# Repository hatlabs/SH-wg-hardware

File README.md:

# Sailor Hat WiFi Gateway

This repository contains the Sailor Hat WiFi Gateway (SH-wg) hardware design. SH-wg is a purpose-built NMEA 2000 WiFi gateway device.

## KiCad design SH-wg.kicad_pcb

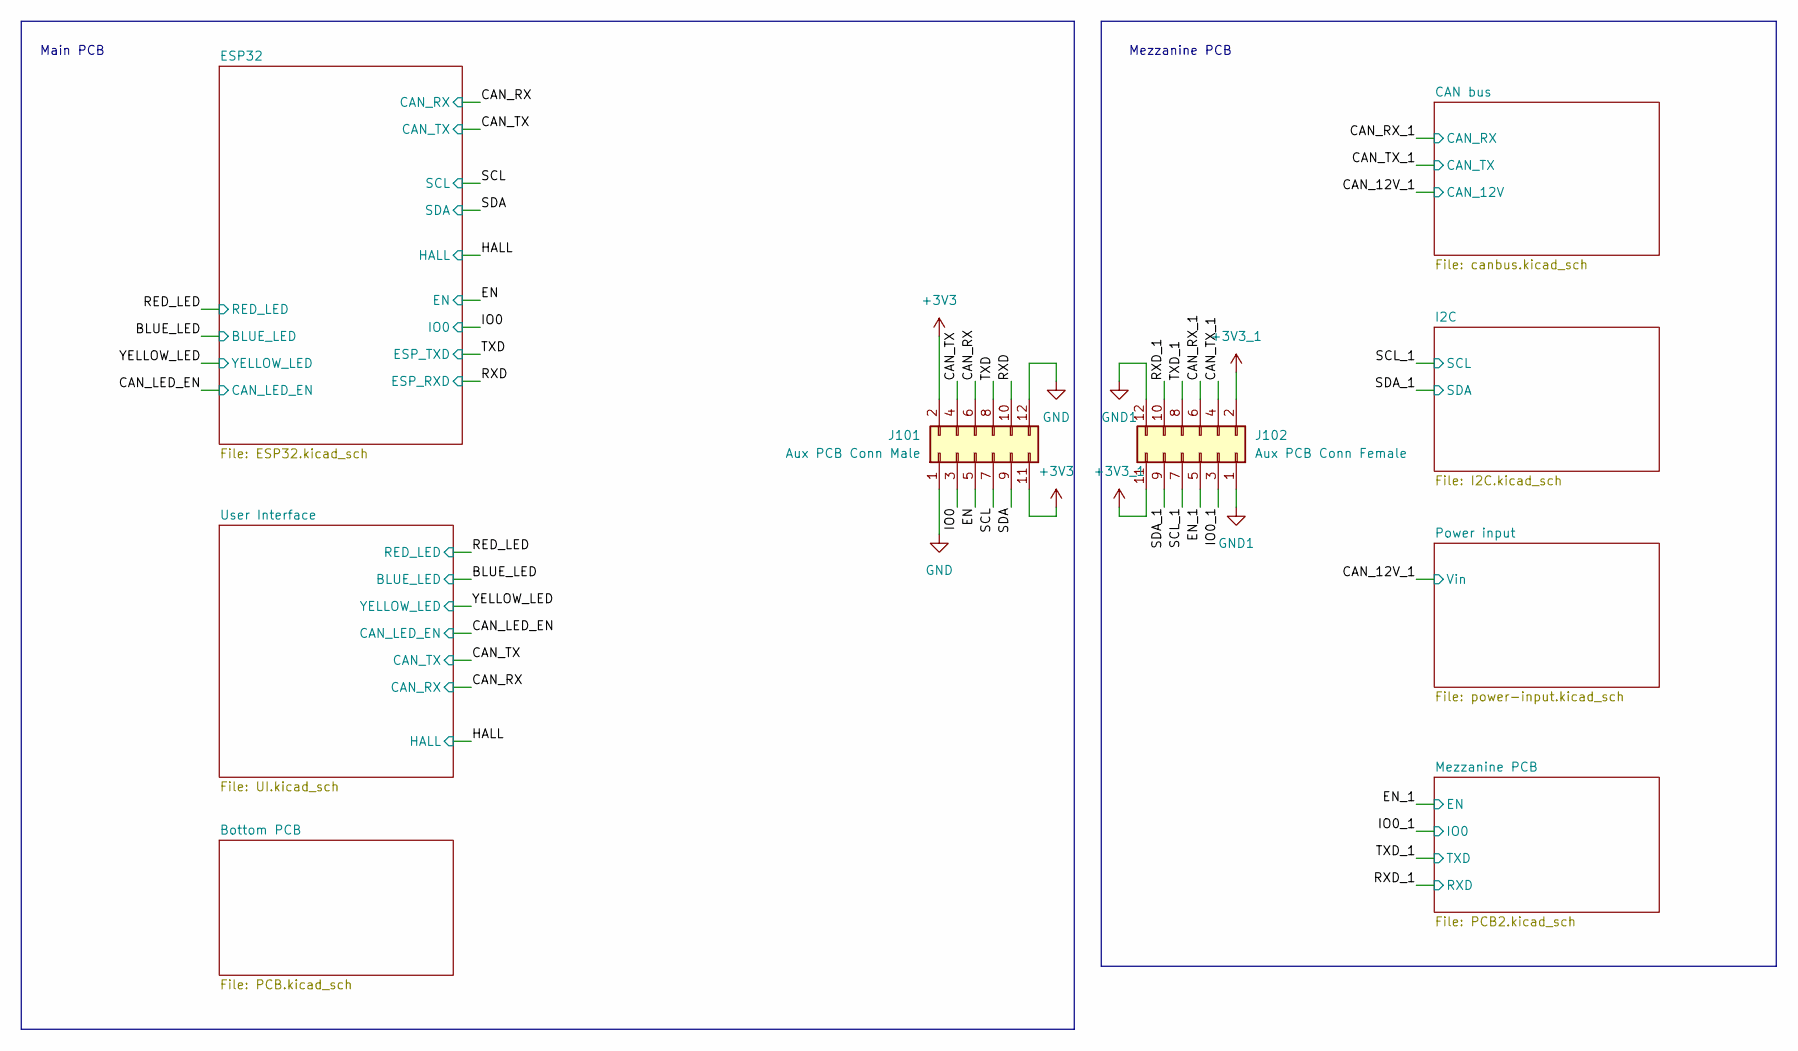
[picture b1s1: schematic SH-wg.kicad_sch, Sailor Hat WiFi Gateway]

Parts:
J101: Aux PCB Conn Male; PinHeader_2x06_P2.54mm_Vertical; LCSC C124388
J102: Aux PCB Conn Female; PinSocket_2x06_P2.54mm_Vertical; LCSC C36191

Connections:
+3V3_1: J102.2, J102.11; also elsewhere on the board
/CAN_RX: J101.6; also elsewhere on the board
/CAN_RX_1: J102.6; also elsewhere on the board
/CAN_TX: J101.4; also elsewhere on the board
/CAN_TX_1: J102.4; also elsewhere on the board
/EN: J101.5; also elsewhere on the board
/EN_1: J102.5; also elsewhere on the board
/IO0: J101.3; also elsewhere on the board
/IO0_1: J102.3; also elsewhere on the board
/RXD: J101.10; also elsewhere on the board
/RXD_1: J102.10; also elsewhere on the board
/SCL: J101.7; also elsewhere on the board
/SCL_1: J102.7; also elsewhere on the board
/SDA: J101.9; also elsewhere on the board
/SDA_1: J102.9; also elsewhere on the board
/TXD: J101.8; also elsewhere on the board
/TXD_1: J102.8; also elsewhere on the board
GND: J101.1, J101.12; also elsewhere on the board
GND1: J102.1, J102.12; also elsewhere on the board

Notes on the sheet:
Mezzanine PCB
Main PCB

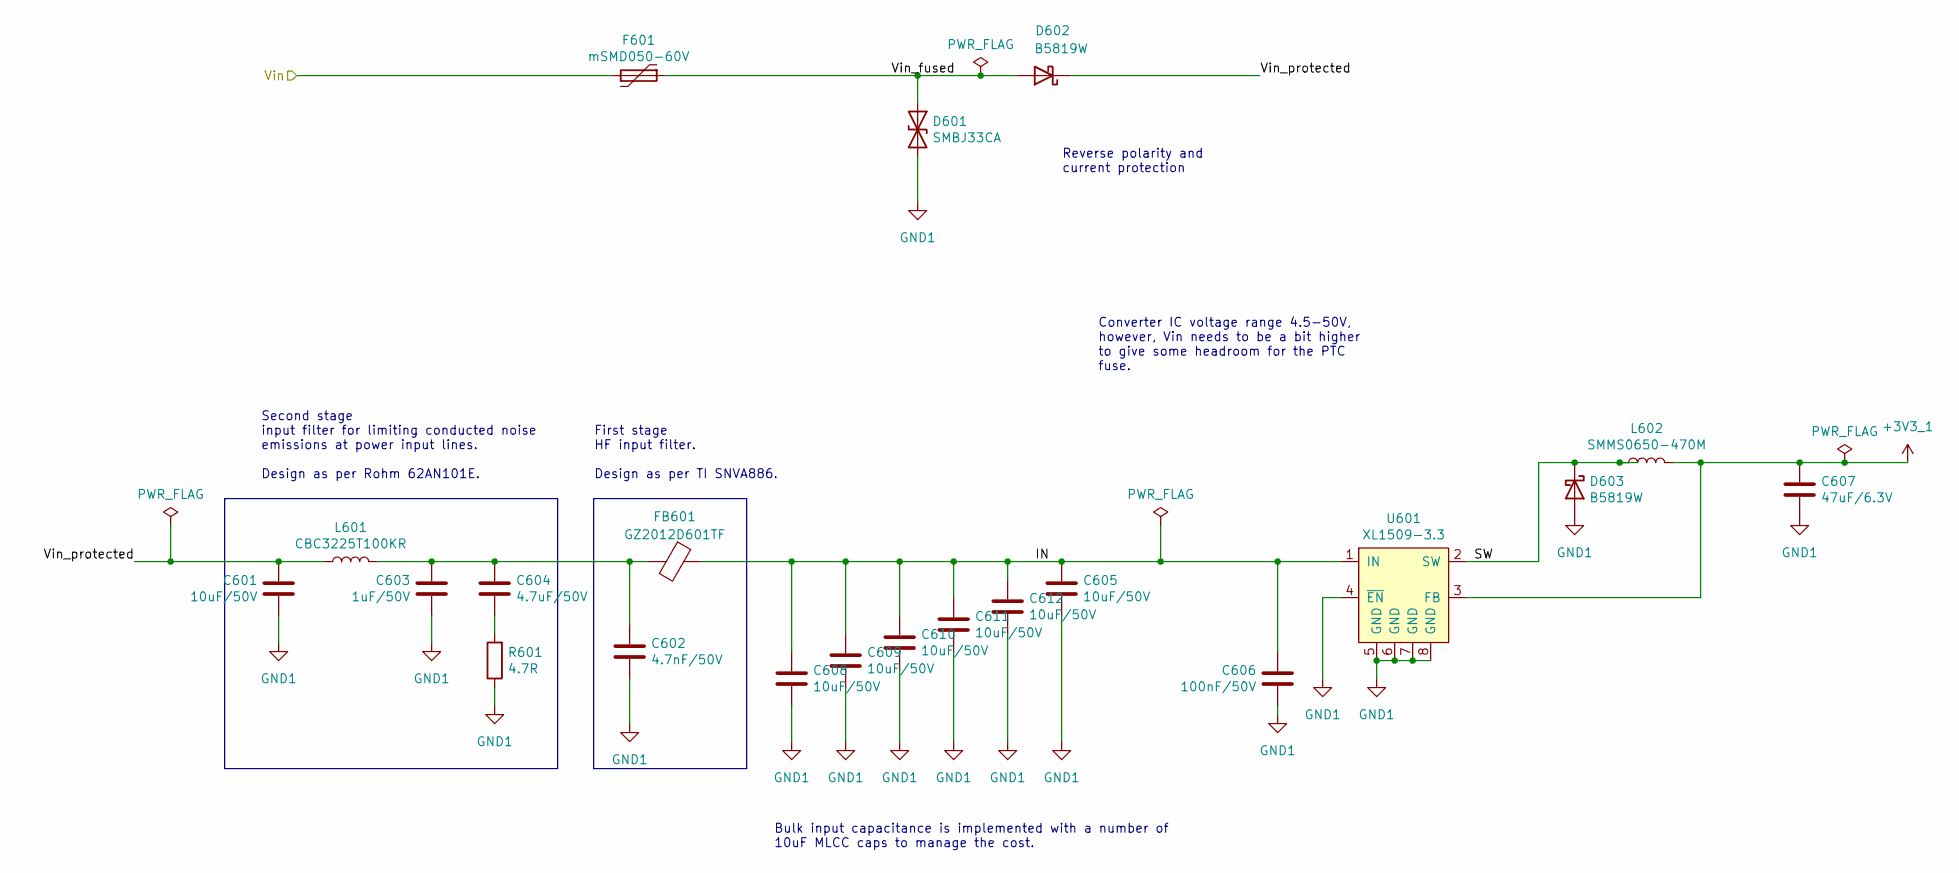
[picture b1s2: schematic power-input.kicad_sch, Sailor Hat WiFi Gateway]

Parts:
C601, C605, C608, C609, C610, C611, C612: 10uF/50V; C_1206_3216Metric; LCSC C13585
C602: 4.7nF/50V; C_0402_1005Metric; LCSC C1538
C603: 1uF/50V; C_0805_2012Metric; LCSC C215803
C604: 4.7uF/50V; C_1206_3216Metric; LCSC C29823
C606: 100nF/50V; C_0402_1005Metric; LCSC C307331
C607: 47uF/6.3V; C_1206_3216Metric; LCSC C96123
D601: SMBJ33CA; D_SMB; LCSC C114000
D602, D603: B5819W; D_SOD-123F; LCSC C8598
F601: mSMD050-60V; Fuse_1812_4532Metric; LCSC C70113
FB601: GZ2012D601TF; L_0805_2012Metric; LCSC C1017
L601: CBC3225T100KR; L_1210_3225Metric; LCSC C90321
L602: SMMS0650-470M; SMMS0650-1R0M; LCSC C149588
R601: 4.7R; R_0603_1608Metric; LCSC C23164
U601: XL1509-3.3; SOP-8_3.9x4.9mm_P1.27mm; LCSC C2681226

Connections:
+3V3_1: C607.1, L602.2, U601.3 (FB); also elsewhere on the board
/CAN_12V_1: F601.2; also elsewhere on the board
/Power input/IN: C605.1, C606.1, C608.1, C609.1, C610.1, C611.1, C612.1, FB601.1, U601.1 (IN)
/Power input/SW: D603.1 (K), L602.1, U601.2 (SW)
/Power input/Vin_fused: D601.1 (A1), D602.2 (A), F601.1
/Power input/Vin_protected: C601.2, D602.1 (K), L601.1
GND1: C601.1, C602.2, C603.1, C605.2, C606.2, C607.2, C608.2, C609.2, C610.2, C611.2, C612.2, D601.2 (A2), D603.2 (A), R601.1, U601.4 (~EN), U601.5 (GND), U601.6 (GND), U601.7 (GND), U601.8 (GND); also elsewhere on the board
unnamed: C602.1, C603.2, C604.1, FB601.2, L601.2
unnamed: C604.2, R601.2

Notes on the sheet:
Second stage input filter for limiting conducted noise emissions at power input lines. Design as per Rohm 62AN101E.
Converter IC voltage range 4.5-50V, however, Vin needs to be a bit higher to give some headroom for the PTC fuse.
First stage HF input filter. Design as per TI SNVA886.
Bulk input capacitance is implemented with a number of 10uF MLCC caps to manage the cost.
Reverse polarity and current protection

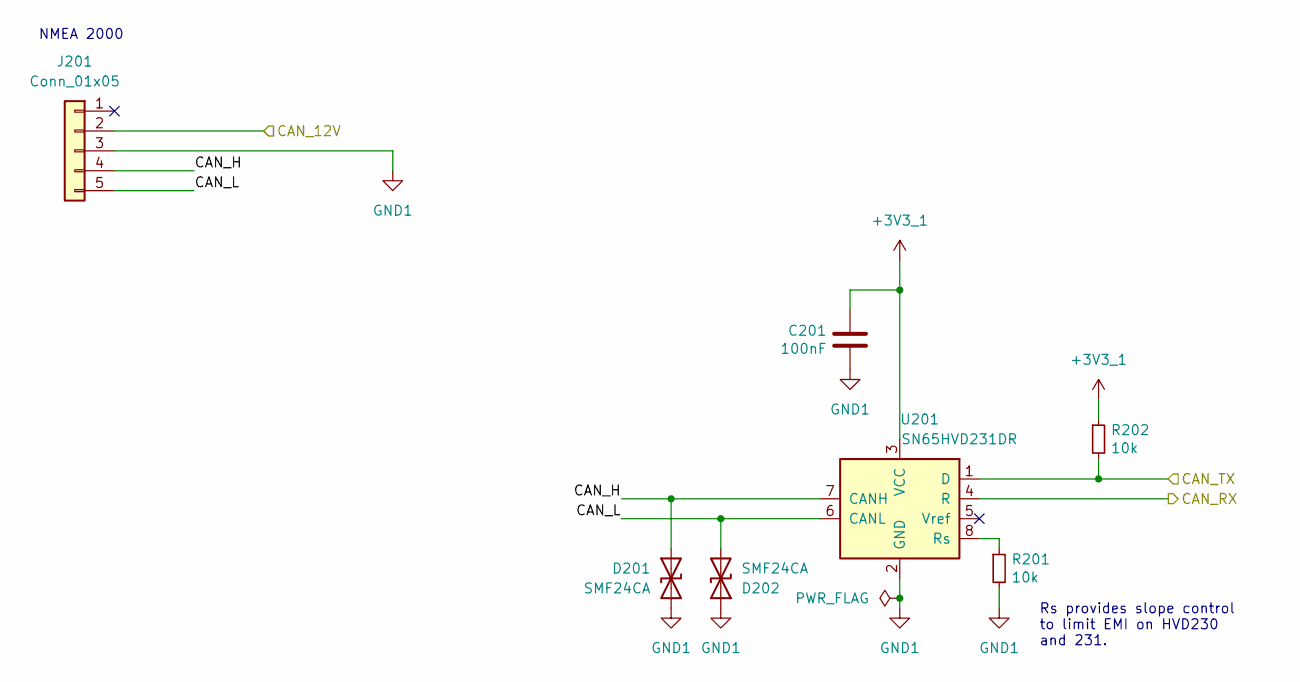
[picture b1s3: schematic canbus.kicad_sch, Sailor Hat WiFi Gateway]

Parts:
C201: 100nF; C_0402_1005Metric; LCSC C1525
D201, D202: SMF24CA; D_SOD-123F; LCSC C353294
J201: Conn_01x05; M12-5A_Male_Horizontal_PCB_Hysik
R201, R202: 10k; R_0402_1005Metric; LCSC C25744
U201: SN65HVD231DR; SOIC-8_3.9x4.9mm_P1.27mm; LCSC C129257

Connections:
+3V3_1: C201.1, R202.1, U201.3 (VCC); also elsewhere on the board
/CAN bus/CAN_H: D201.1 (A1), J201.4, U201.7 (CANH)
/CAN bus/CAN_L: D202.2 (A2), J201.5, U201.6 (CANL)
/CAN_12V_1: J201.2; also elsewhere on the board
/CAN_RX_1: U201.4 (R); also elsewhere on the board
/CAN_TX_1: R202.2, U201.1 (D); also elsewhere on the board
GND1: C201.2, D201.2 (A2), D202.1 (A1), J201.3, R201.2, U201.2 (GND); also elsewhere on the board
unnamed: R201.1, U201.8 (Rs)

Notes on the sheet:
Rs provides slope control to limit EMI on HVD230 and 231.
NMEA 2000

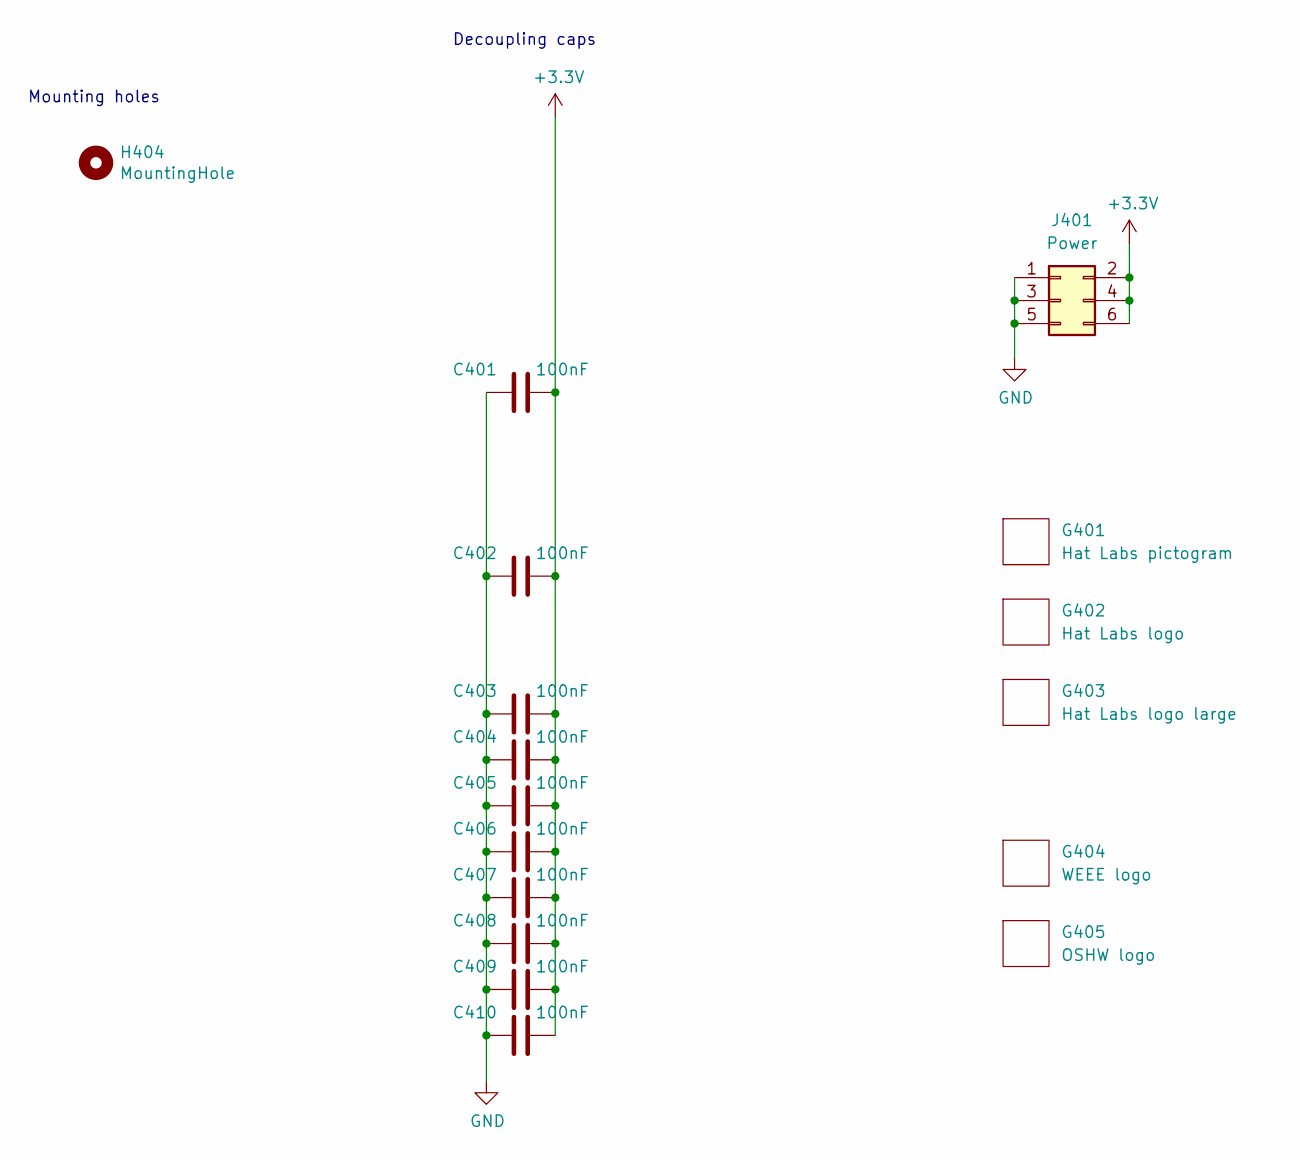
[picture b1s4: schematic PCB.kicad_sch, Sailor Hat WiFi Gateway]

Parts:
C401, C402, C403, C404, C405, C406, C407, C408, C409, C410: 100nF; C_0402_1005Metric; LCSC C1525
G401: Hat Labs pictogram; HL_pictogram_6.3mm
G402: Hat Labs logo; Hat_Labs_20mm
G403: Hat Labs logo large; Hat_Labs_25.4mm
G404: WEEE logo; WEEE-Logo_5.6x8mm_SilkScreen
G405: OSHW logo; OSHW-Logo2_9.8x8mm_SilkScreen
H404: MountingHole; MountingHole_3.2mm_M3_no_copper
J401: Power; PinHeader_2x03_P2.54mm_Vertical; LCSC C65114

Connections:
GND: C401.1, C402.1, C403.1, C404.1, C405.1, C406.1, C407.1, C408.1, C409.1, C410.1, J401.1, J401.3, J401.5; also elsewhere on the board

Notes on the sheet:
Mounting holes
Decoupling caps

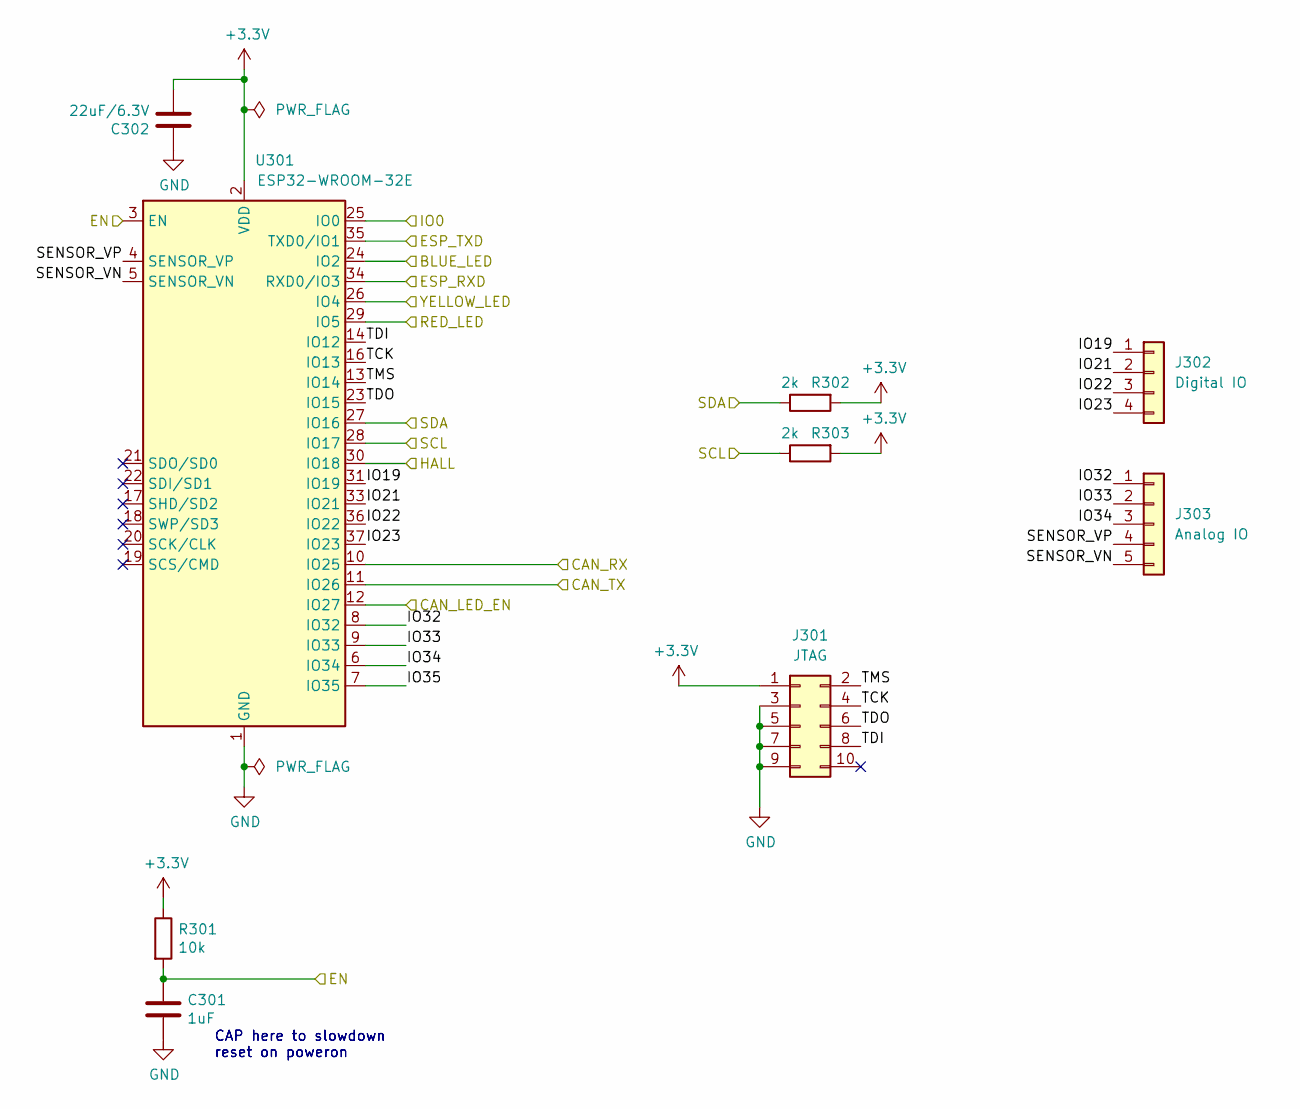
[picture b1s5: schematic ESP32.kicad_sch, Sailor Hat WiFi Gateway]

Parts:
C301: 1uF; C_0402_1005Metric; LCSC C52923
C302: 22uF/6.3V; C_0603_1608Metric; LCSC C59461
J301: JTAG; IDC-Header_2x05_P2.54mm_Vertical; LCSC C5665
J302: Digital IO; PinHeader_1x04_P2.54mm_Vertical; LCSC C358686
J303: Analog IO; PinHeader_1x05_P2.54mm_Vertical; LCSC C124379
R301: 10k; R_0402_1005Metric; LCSC C25744
R302, R303: 2k; R_0402_1005Metric; LCSC C4109
U301: ESP32-WROOM-32E; ESP32-WROOM-32-HandSolder; LCSC C701341

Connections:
/BLUE_LED: U301.24 (IO2); also elsewhere on the board
/CAN_LED_EN: U301.12 (IO27); also elsewhere on the board
/CAN_RX: U301.10 (IO25); also elsewhere on the board
/CAN_TX: U301.11 (IO26); also elsewhere on the board
/EN: C301.1, R301.2, U301.3 (EN); also elsewhere on the board
/ESP32/IO19: J302.1, U301.31 (IO19)
/ESP32/IO21: J302.2, U301.33 (IO21)
/ESP32/IO22: J302.3, U301.36 (IO22)
/ESP32/IO23: J302.4, U301.37 (IO23)
/ESP32/IO32: J303.1, U301.8 (IO32)
/ESP32/IO33: J303.2, U301.9 (IO33)
/ESP32/IO34: J303.3, U301.6 (IO34)
/ESP32/IO35: U301.7 (IO35)
/ESP32/SENSOR_VN: J303.5, U301.5 (SENSOR_VN)
/ESP32/SENSOR_VP: J303.4, U301.4 (SENSOR_VP)
/ESP32/TCK: J301.4, U301.16 (IO13)
/ESP32/TDI: J301.8, U301.14 (IO12)
/ESP32/TDO: J301.6, U301.23 (IO15)
/ESP32/TMS: J301.2, U301.13 (IO14)
/HALL: U301.30 (IO18); also elsewhere on the board
/IO0: U301.25 (IO0); also elsewhere on the board
/RED_LED: U301.29 (IO5); also elsewhere on the board
/RXD: U301.34 (RXD0/IO3); also elsewhere on the board
/SCL: R303.1, U301.28 (IO17); also elsewhere on the board
/SDA: R302.1, U301.27 (IO16); also elsewhere on the board
/TXD: U301.35 (TXD0/IO1); also elsewhere on the board
/YELLOW_LED: U301.26 (IO4); also elsewhere on the board
GND: C301.2, C302.1, J301.3, J301.5, J301.7, J301.9, U301.1 (GND), U301.15 (GND), U301.38 (GND), U301.39 (GND); also elsewhere on the board

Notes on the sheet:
CAP here to slowdown reset on poweron

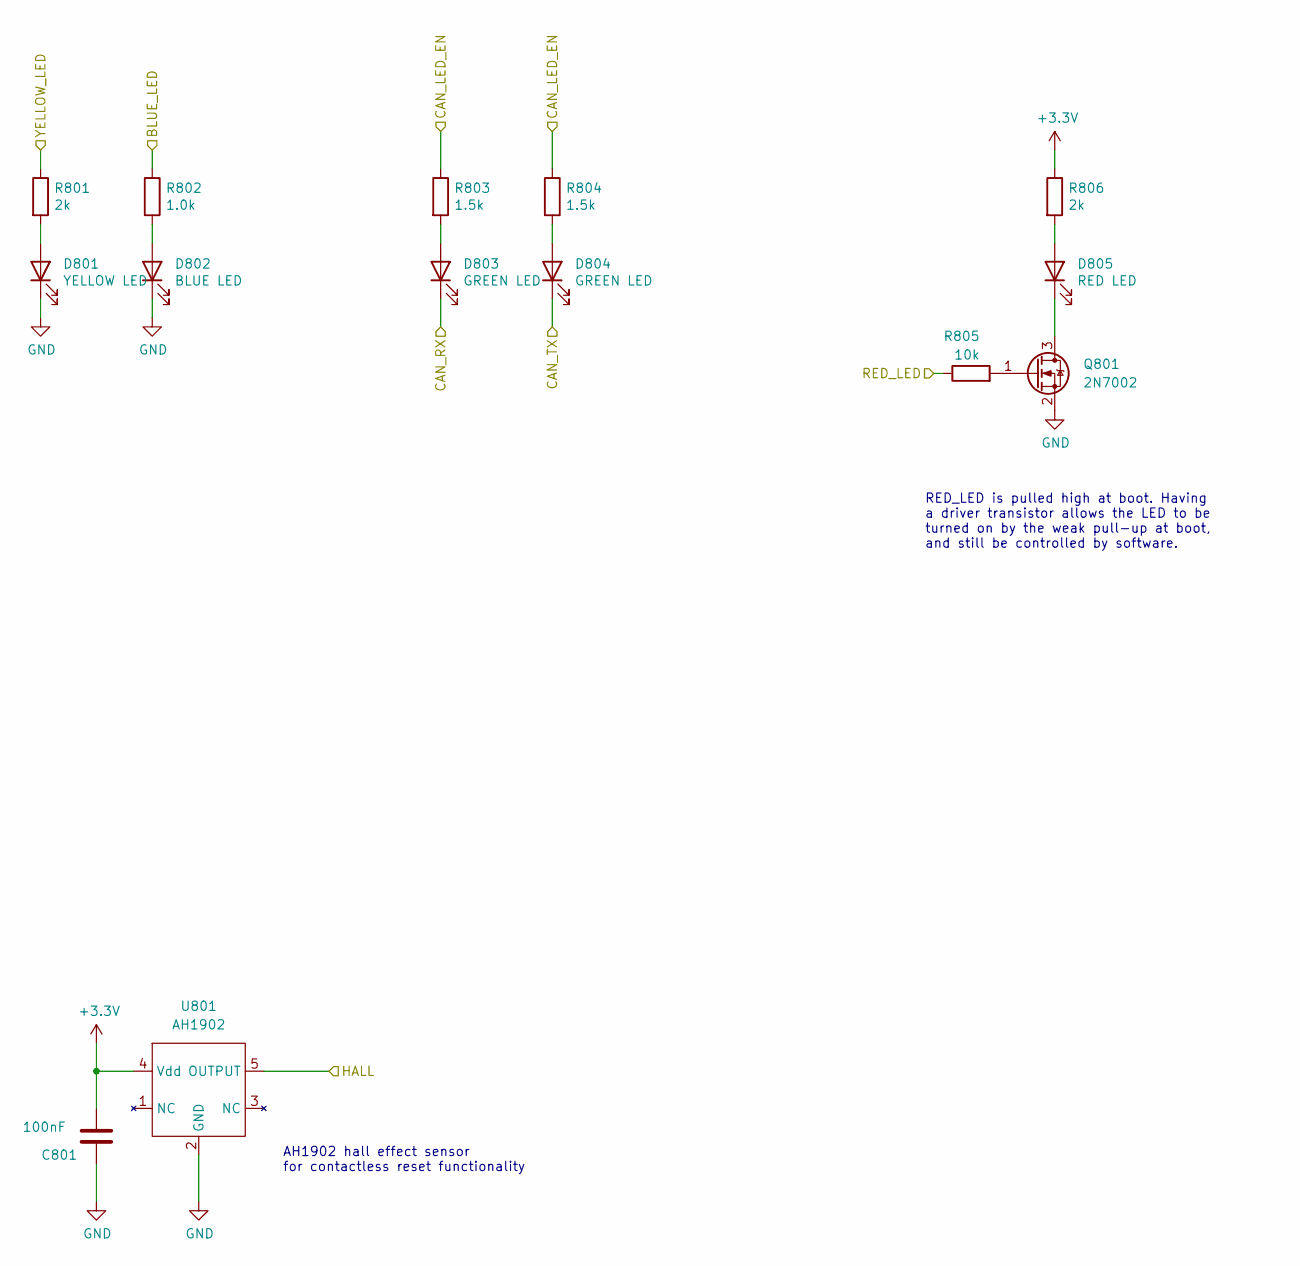
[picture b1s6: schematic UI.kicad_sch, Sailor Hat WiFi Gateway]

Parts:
C801: 100nF; C_0402_1005Metric; LCSC C1525
D801: YELLOW LED; LED_0603_1608Metric; LCSC C72038
D802: BLUE LED; LED_0603_1608Metric; LCSC C72041
D803, D804: GREEN LED; LED_0603_1608Metric; LCSC C72043
D805: RED LED; LED_0603_1608Metric; LCSC C2286
Q801: 2N7002; SOT-23; LCSC C8545
R801, R806: 2k; R_0402_1005Metric; LCSC C4109
R802: 1.0k; R_0402_1005Metric; LCSC C11702
R803, R804: 1.5k; R_0402_1005Metric; LCSC C25867
R805: 10k; R_0402_1005Metric; LCSC C25744
U801: AH1902; SOT-553; LCSC C239188

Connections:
/BLUE_LED: R802.1; also elsewhere on the board
/CAN_LED_EN: R803.1, R804.1; also elsewhere on the board
/CAN_RX: D803.1 (K); also elsewhere on the board
/CAN_TX: D804.1 (K); also elsewhere on the board
/HALL: U801.5 (OUTPUT); also elsewhere on the board
/RED_LED: R805.1; also elsewhere on the board
/YELLOW_LED: R801.1; also elsewhere on the board
GND: C801.1, D801.1 (K), D802.1 (K), Q801.2 (S), U801.2 (GND); also elsewhere on the board
unnamed: D801.2 (A), R801.2
unnamed: D802.2 (A), R802.2
unnamed: D803.2 (A), R803.2
unnamed: D804.2 (A), R804.2
unnamed: D805.1 (K), Q801.3 (D)
unnamed: D805.2 (A), R806.2
unnamed: Q801.1 (G), R805.2

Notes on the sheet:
AH1902 hall effect sensor for contactless reset functionality
RED_LED is pulled high at boot. Having a driver transistor allows the LED to be turned on by the weak pull-up at boot, and still be controlled by software.

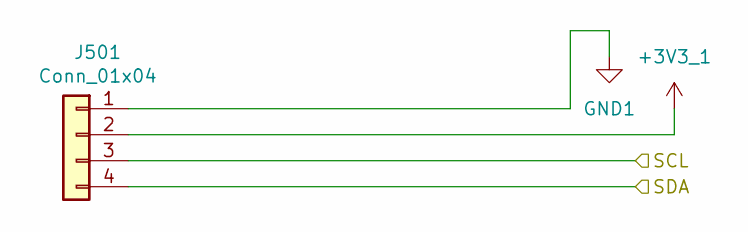
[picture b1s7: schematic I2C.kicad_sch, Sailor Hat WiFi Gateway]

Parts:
J501: Conn_01x04; PinSocket_1x04_P2.54mm_Vertical; LCSC C124413

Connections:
+3V3_1: J501.2; also elsewhere on the board
/SCL_1: J501.3; also elsewhere on the board
/SDA_1: J501.4; also elsewhere on the board
GND1: J501.1; also elsewhere on the board

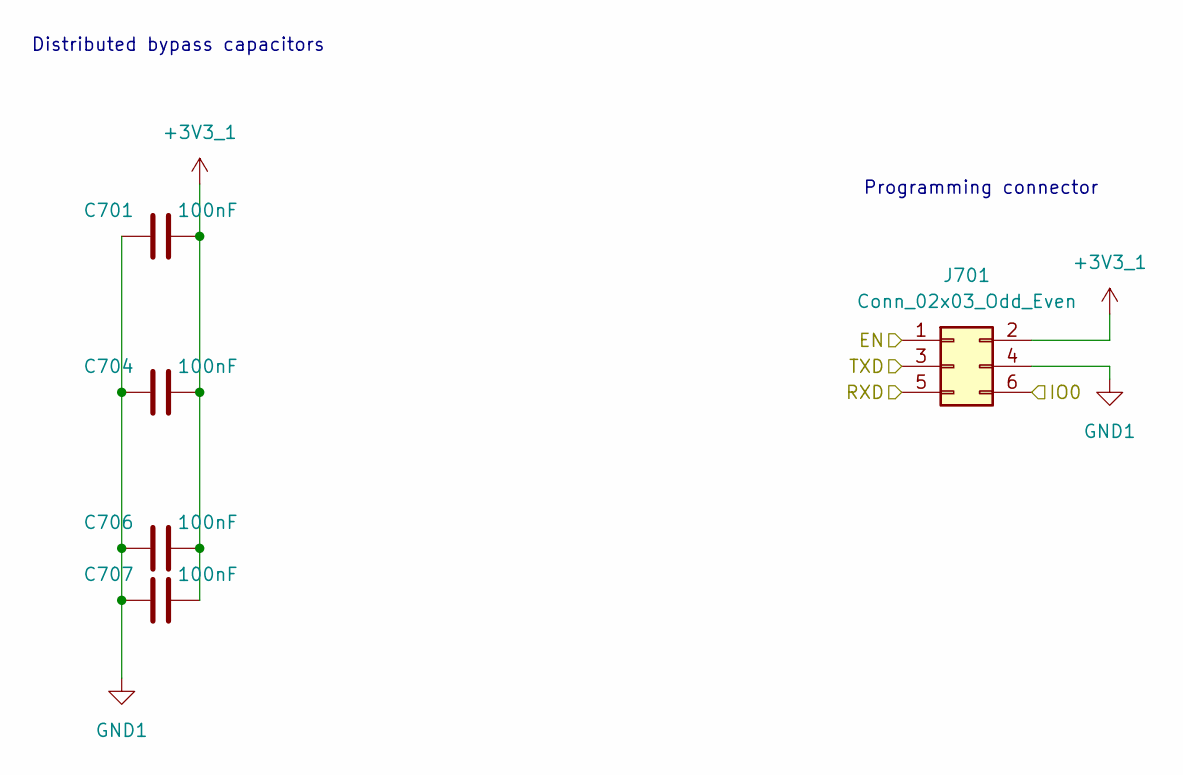
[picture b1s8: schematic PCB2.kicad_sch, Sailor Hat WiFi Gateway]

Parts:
C701, C704, C706, C707: 100nF; C_0402_1005Metric; LCSC C1525
J701: Conn_02x03_Odd_Even; PinHeader_2x03_P2.54mm_Vertical; LCSC C65114

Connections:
+3V3_1: C701.2, C704.2, C706.2, C707.2, J701.2; also elsewhere on the board
/EN_1: J701.1; also elsewhere on the board
/IO0_1: J701.6; also elsewhere on the board
/RXD_1: J701.5; also elsewhere on the board
/TXD_1: J701.3; also elsewhere on the board
GND1: C701.1, C704.1, C706.1, C707.1, J701.4; also elsewhere on the board

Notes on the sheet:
Programming connector
Distributed bypass capacitors

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
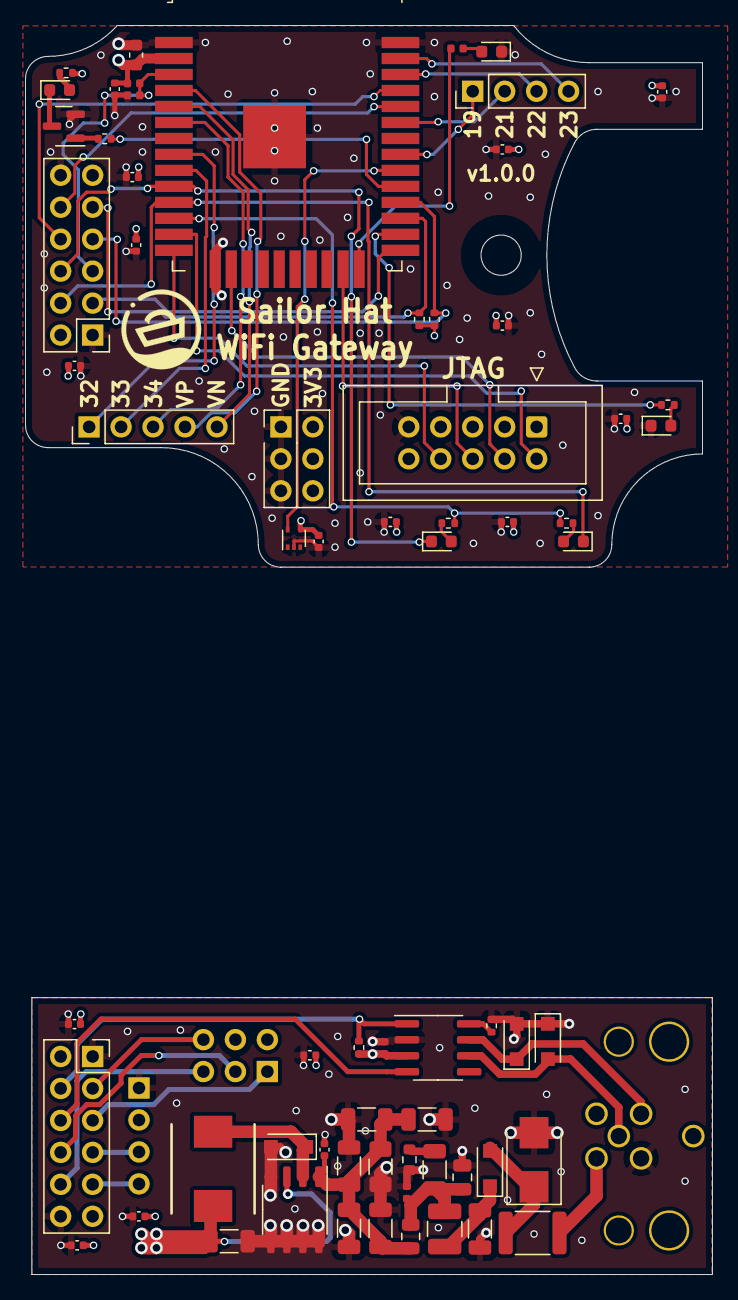
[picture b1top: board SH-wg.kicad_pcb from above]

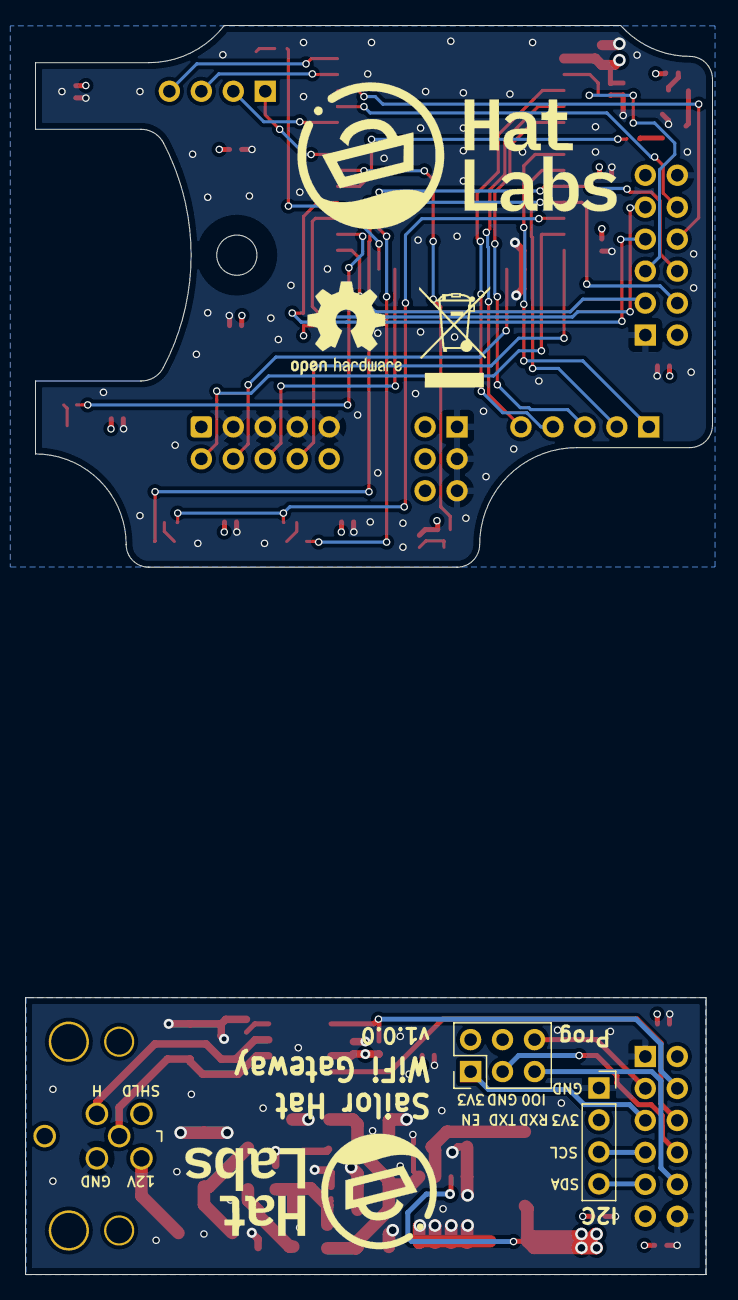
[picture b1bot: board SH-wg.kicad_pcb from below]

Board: 4 copper layers, 54.6 x 99.2 mm, 76 parts (6 on the bottom side), 55 nets.

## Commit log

2022-01-26 Rename and update layout
2022-01-26 Add headers & LEDs
2022-01-28 Finish 0.1.0 design
2022-01-30 Prepare final 0.1.0 proto
2022-01-30 Add panel preparation tools
2022-01-30 Update (remove) documentation
2022-02-07 Add a pull-up resistor to CAN TX line
2022-02-21 Add copper clearance around the mounting hole
    Also make the M12 connector opening 1.5mm wider.
2022-02-23 Update the design based on the test results
2022-02-23 Bump the board version, improve silkscreens
2022-02-24 Update LED resistor values, improve PCB edge clearance
2022-02-24 Chore: C301 value: 1uf -> 1uF
2022-03-17 Bump the version number
2022-03-17 Rename old panelization scripts
2022-03-17 Adjust tab locations
2022-03-17 Change CAN transceiver according to availability
2022-03-17 Tweak tab locations
2022-03-17 Add scripts for panelizing the PCBs
2022-03-17 Update TVS diode LCSC part number

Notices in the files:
ESP32.kicad_sch:
https://creativecommons.org/licenses/by-sa/4.0
SH-ESP32 is licensed under CC BY-SA 4.0.
PCB.kicad_sch:
SH-wg is licensed under CC BY-SA 4.0.
SH-wg.kicad_pcb:
https://creativecommons.org/licenses/by/4.0
SH-wg is licensed under CC BY 4.0.
